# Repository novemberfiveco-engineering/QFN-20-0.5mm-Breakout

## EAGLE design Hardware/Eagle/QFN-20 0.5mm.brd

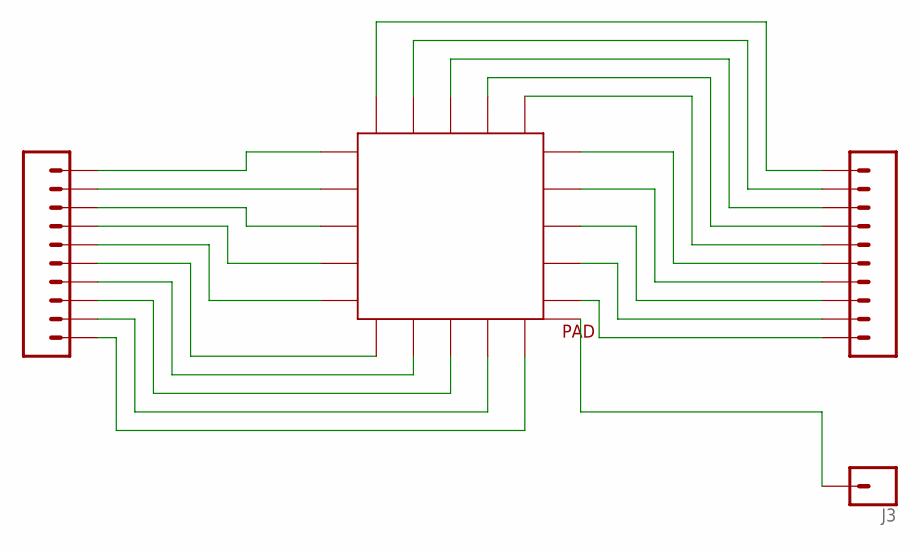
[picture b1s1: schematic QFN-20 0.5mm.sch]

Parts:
J1, J2: CONN_10"; 1X10
J3: CONN_01; 1X01
U$1: QFN-20_0,5MM; QFN20_0,5MM

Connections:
unnamed: J1.1, U$1.1 (PIN1)
unnamed: J1.2, U$1.2 (PIN2)
unnamed: J1.3, U$1.3 (PIN3)
unnamed: J1.4, U$1.4 (PIN4)
unnamed: J1.5, U$1.5 (PIN5)
unnamed: J1.6, U$1.6 (PIN6)
unnamed: J1.7, U$1.7 (PIN7)
unnamed: J1.8, U$1.8 (PIN8)
unnamed: J1.9, U$1.9 (PIN9)
unnamed: J1.10, U$1.10 (PIN10)
unnamed: J3.1, U$1.0 (PAD)
unnamed: J2.10, U$1.11 (PIN11)
unnamed: J2.9, U$1.12 (PIN12)
unnamed: J2.8, U$1.13 (PIN13)
unnamed: J2.7, U$1.14 (PIN14)
unnamed: J2.6, U$1.15 (PIN15)
unnamed: J2.5, U$1.16 (PIN16)
unnamed: J2.4, U$1.17 (PIN17)
unnamed: J2.3, U$1.18 (PIN18)
unnamed: J2.2, U$1.19 (PIN19)
unnamed: J2.1, U$1.20 (PIN20)

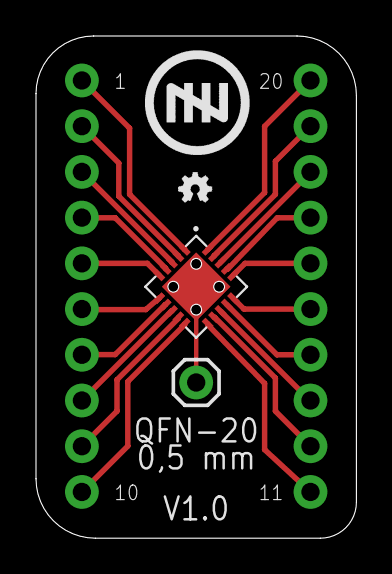
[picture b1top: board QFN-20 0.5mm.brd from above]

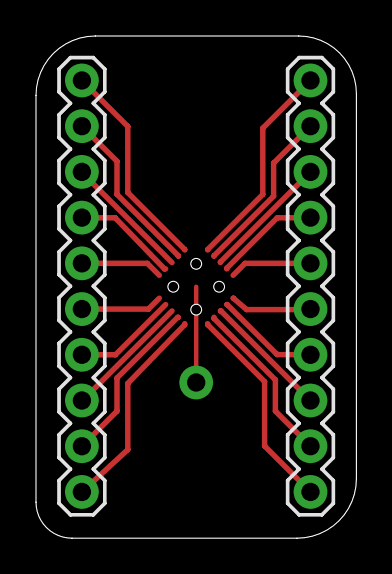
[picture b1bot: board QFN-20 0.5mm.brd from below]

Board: 2 copper layers, 17.8 x 27.9 mm, 6 parts (3 on the bottom side), 21 nets.

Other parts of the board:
U$2: LOGO-NOVEMERFIVE-7SCALE
U$3: LOGO-OSHWA

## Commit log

2017-05-15 Added project library

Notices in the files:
parts and their libraries:
SparkFun-Connectors: Licensing: Creative Commons ShareAlike 4.0 International - https://creativecommons.org/licenses/by-sa/4.0
